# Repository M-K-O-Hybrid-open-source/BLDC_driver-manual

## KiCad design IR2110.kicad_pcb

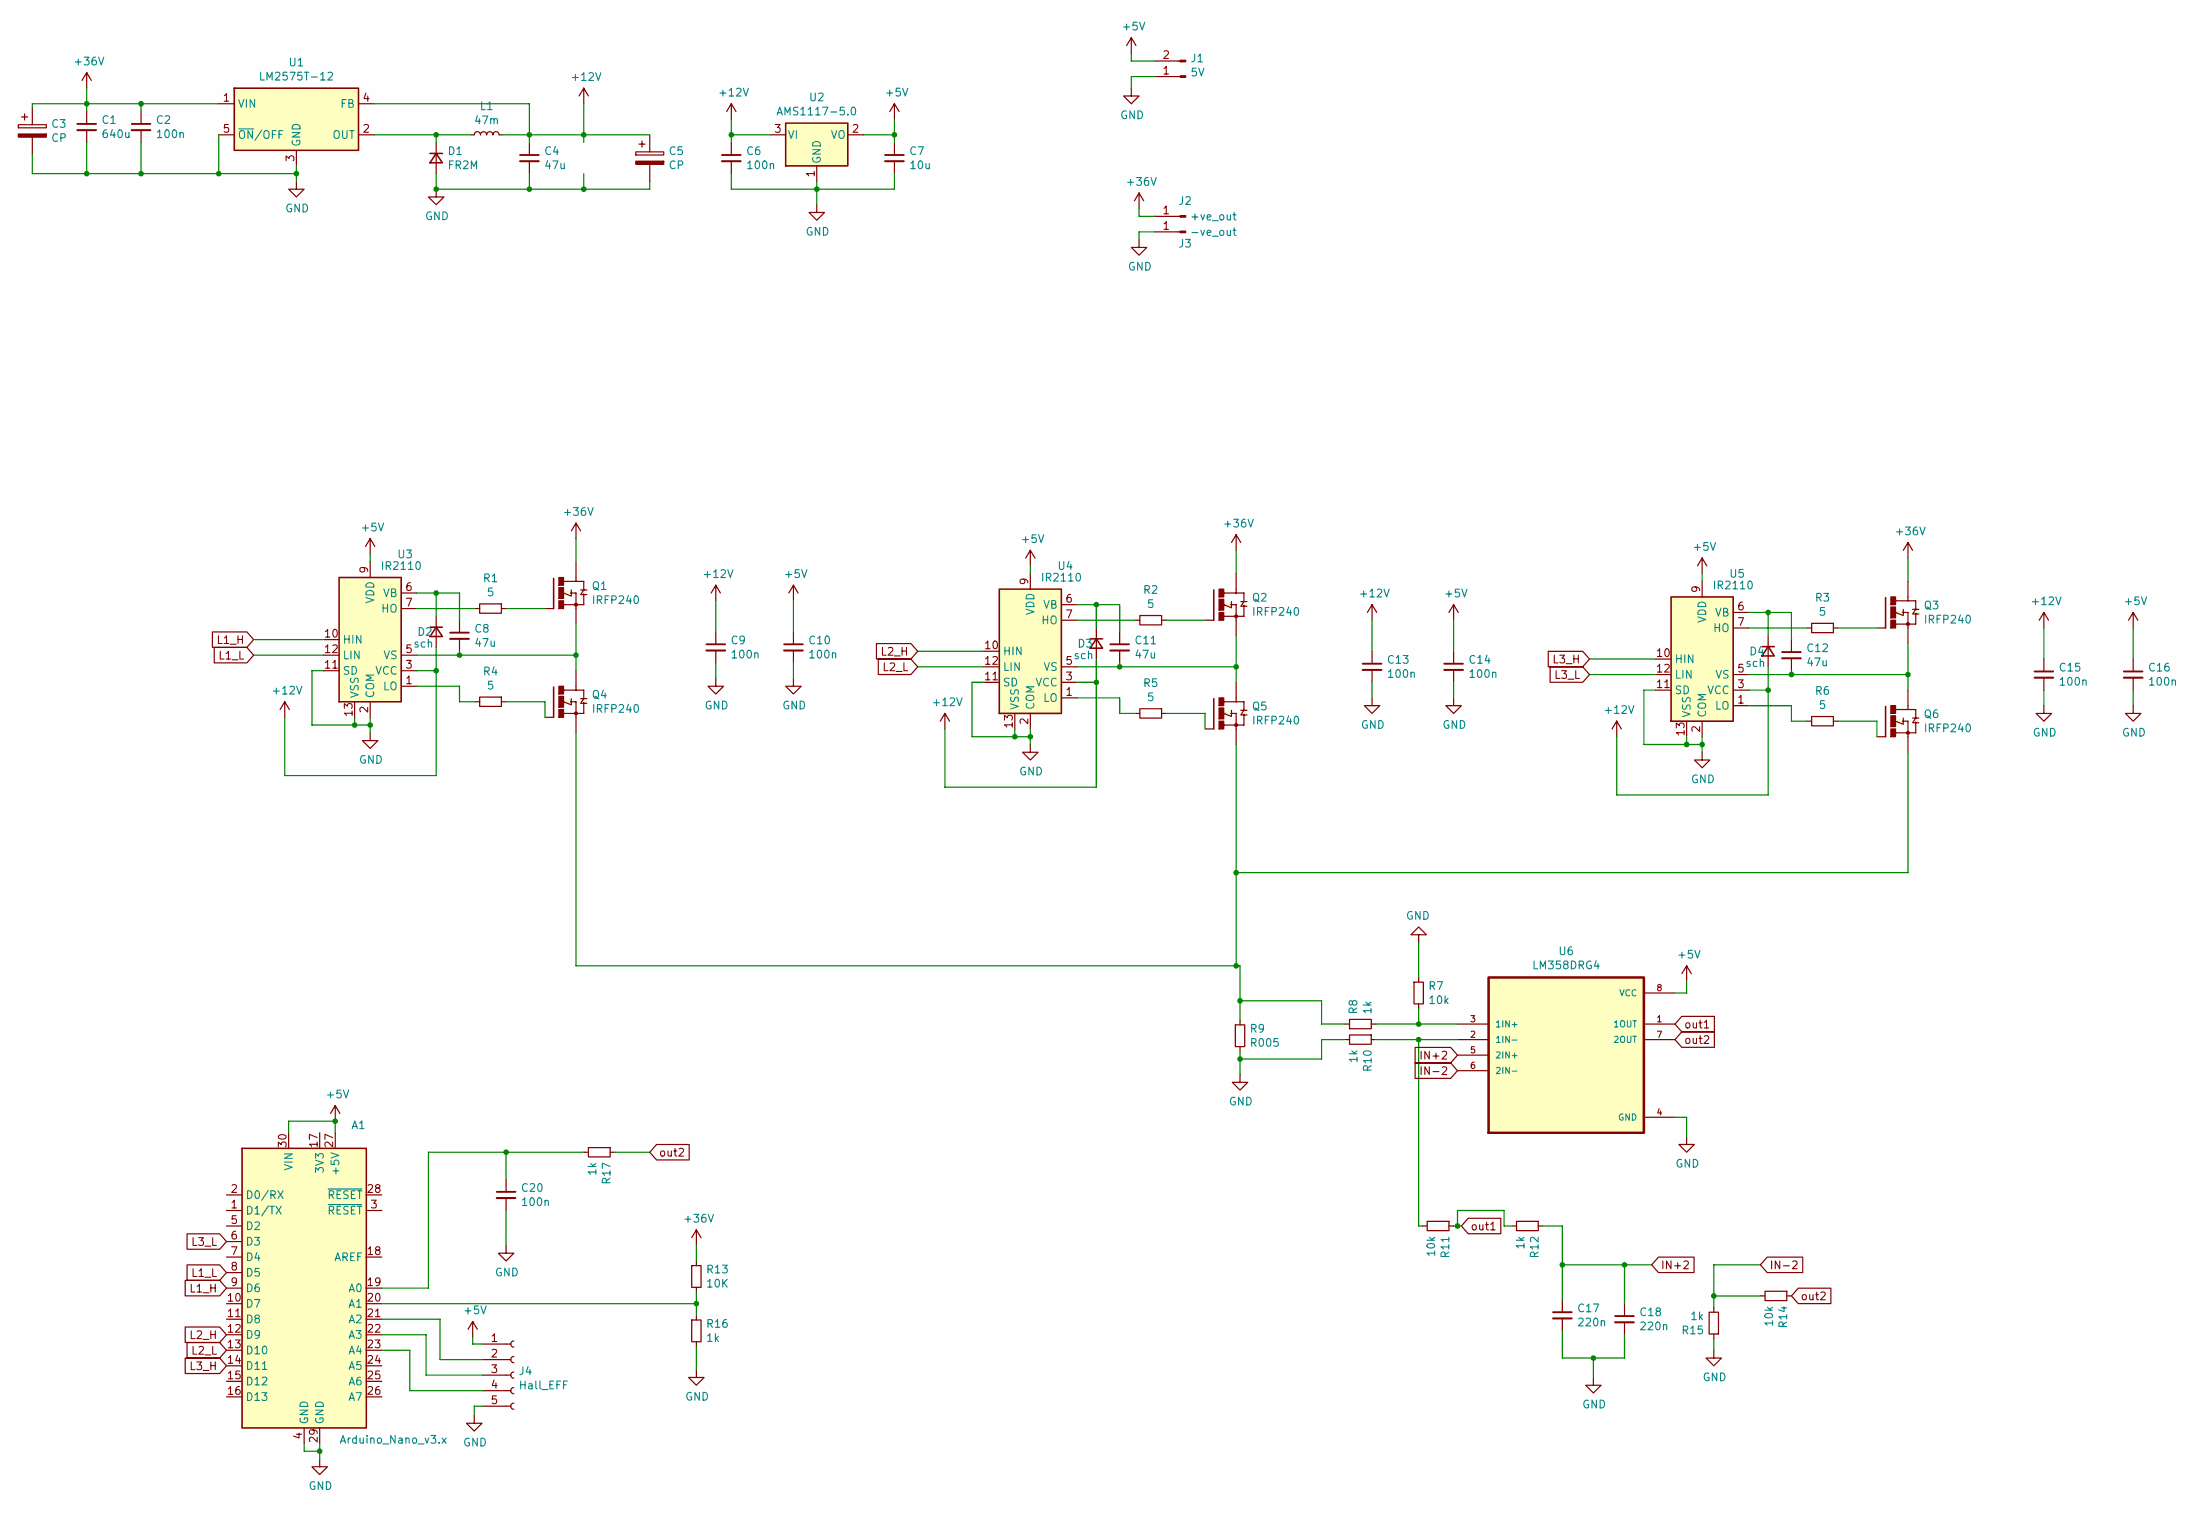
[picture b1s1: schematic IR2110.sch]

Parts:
A1: Arduino_Nano_v3.x; Arduino_Nano
C1: 640u; C_0805_2012Metric
C2, C6, C9, C10, C13, C14, C15, C16, C20: 100n; C_0805_2012Metric
C3, C5: CP; CP_Radial_D8.0mm_P5.00mm
C4, C8, C11, C12: 47u; C_0805_2012Metric
C7: 10u; C_0805_2012Metric
C17, C18: 220n; C_0805_2012Metric
D1: FR2M; D_SMB
D2, D3, D4: sch; D_SMB
J1: 5V; PinSocket_1x02_P2.54mm_Vertical
J2: +ve_out; SolderWirePad_1x01_SMD_1x2mm
J3: -ve_out; SolderWirePad_1x01_SMD_1x2mm
J4: Hall_EFF; PinHeader_1x05_P2.54mm_Vertical
L1: 47m; L_Toroid_Horizontal_D3.2mm_P6.40mm_Diameter3-5mm_Amidon-T12
Q1, Q2, Q3, Q4, Q5, Q6: IRFP240; TO-247-3_Vertical; PARTREV B
R1, R2, R3, R4, R5, R6: 5; R_Axial_DIN0204_L3.6mm_D1.6mm_P1.90mm_Vertical
R7, R11, R14: 10k; R_0805_2012Metric
R8, R10, R12, R15, R16, R17: 1k; R_0805_2012Metric
R9: R005; R_2512_6332Metric
R13: 10K; R_0805_2012Metric
U1: LM2575T-12; TO-220F-5_P3.4x3.7mm_StaggerEven_Lead3.5mm_Vertical
U2: AMS1117-5.0; SOT-223-3_TabPin2
U3, U4, U5: IR2110; DIP-14_W7.62mm
U6: LM358DRG4; SOIC127P599X175-8N

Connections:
+5V: A1.27 (+5V), A1.30 (VIN), C7.1, C10.1, C14.1, C16.1, J1.2, J4.1, U2.2 (VO), U3.9 (VDD), U4.9 (VDD), U5.9 (VDD), U6.8 (VCC)
+12V: C4.1, C5.1, C6.1, C9.1, C13.1, C15.1, D2.2 (A), D3.2 (A), D4.2 (A), L1.2, U1.4 (FB), U2.3 (VI), U3.3 (VCC), U4.3 (VCC), U5.3 (VCC)
+36V: C1.1, C2.1, C3.1, J2.1, Q1.2, Q2.2, Q3.2, R13.1, U1.1 (VIN)
GND: A1.4 (GND), A1.29 (GND), C1.2, C2.2, C3.2, C4.2, C5.2, C6.2, C7.2, C9.2, C10.2, C13.2, C14.2, C15.2, C16.2, C17.2, C18.2, C20.2, D1.2 (A), J1.1, J3.1, J4.5, R7.1, R9.2, R10.2, R15.1, R16.2, U1.3 (GND), U1.5 (~ON~/OFF), U2.1 (GND), U3.2 (COM), U3.11 (SD), U3.13 (VSS), U4.2 (COM), U4.11 (SD), U4.13 (VSS), U5.2 (COM), U5.11 (SD), U5.13 (VSS), U6.4 (GND)
IN+2: C17.1, C18.1, R12.1, U6.5 (2IN+)
IN-2: R14.2, R15.2, U6.6 (2IN-)
L1_H: A1.9 (D6), U3.10 (HIN)
L1_L: A1.8 (D5), U3.12 (LIN)
L2_H: A1.12 (D9), U4.10 (HIN)
L2_L: A1.13 (D10), U4.12 (LIN)
L3_H: A1.14 (D11), U5.10 (HIN)
L3_L: A1.6 (D3), U5.12 (LIN)
unnamed: A1.19 (A0), C20.1, R17.2
unnamed: A1.20 (A1), R13.2, R16.1
unnamed: A1.21 (A2), J4.2
unnamed: A1.22 (A3), J4.3
unnamed: A1.23 (A4), J4.4
unnamed: C8.1, D2.1 (K), U3.6 (VB)
unnamed: C8.2, Q1.3, Q4.2, U3.5 (VS)
unnamed: C11.1, D3.1 (K), U4.6 (VB)
unnamed: C11.2, Q2.3, Q5.2, U4.5 (VS)
unnamed: C12.1, D4.1 (K), U5.6 (VB)
unnamed: C12.2, Q3.3, Q6.2, U5.5 (VS)
unnamed: D1.1 (K), L1.1, U1.2 (OUT)
unnamed: Q1.1, R1.1
unnamed: Q2.1, R2.1
unnamed: Q3.1, R3.1
unnamed: Q4.1, R4.1
unnamed: Q4.3, Q5.3, Q6.3, R8.1, R9.1
unnamed: Q5.1, R5.1
unnamed: Q6.1, R6.1
unnamed: R1.2, U3.7 (HO)
unnamed: R2.2, U4.7 (HO)
unnamed: R3.2, U5.7 (HO)
unnamed: R4.2, U3.1 (LO)
unnamed: R5.2, U4.1 (LO)
unnamed: R6.2, U5.1 (LO)
unnamed: R7.2, R8.2, U6.3 (1IN+)
unnamed: R10.1, R11.2, U6.2 (1IN-)
out1: R11.1, R12.2, U6.1 (1OUT)
out2: R14.1, R17.1, U6.7 (2OUT)

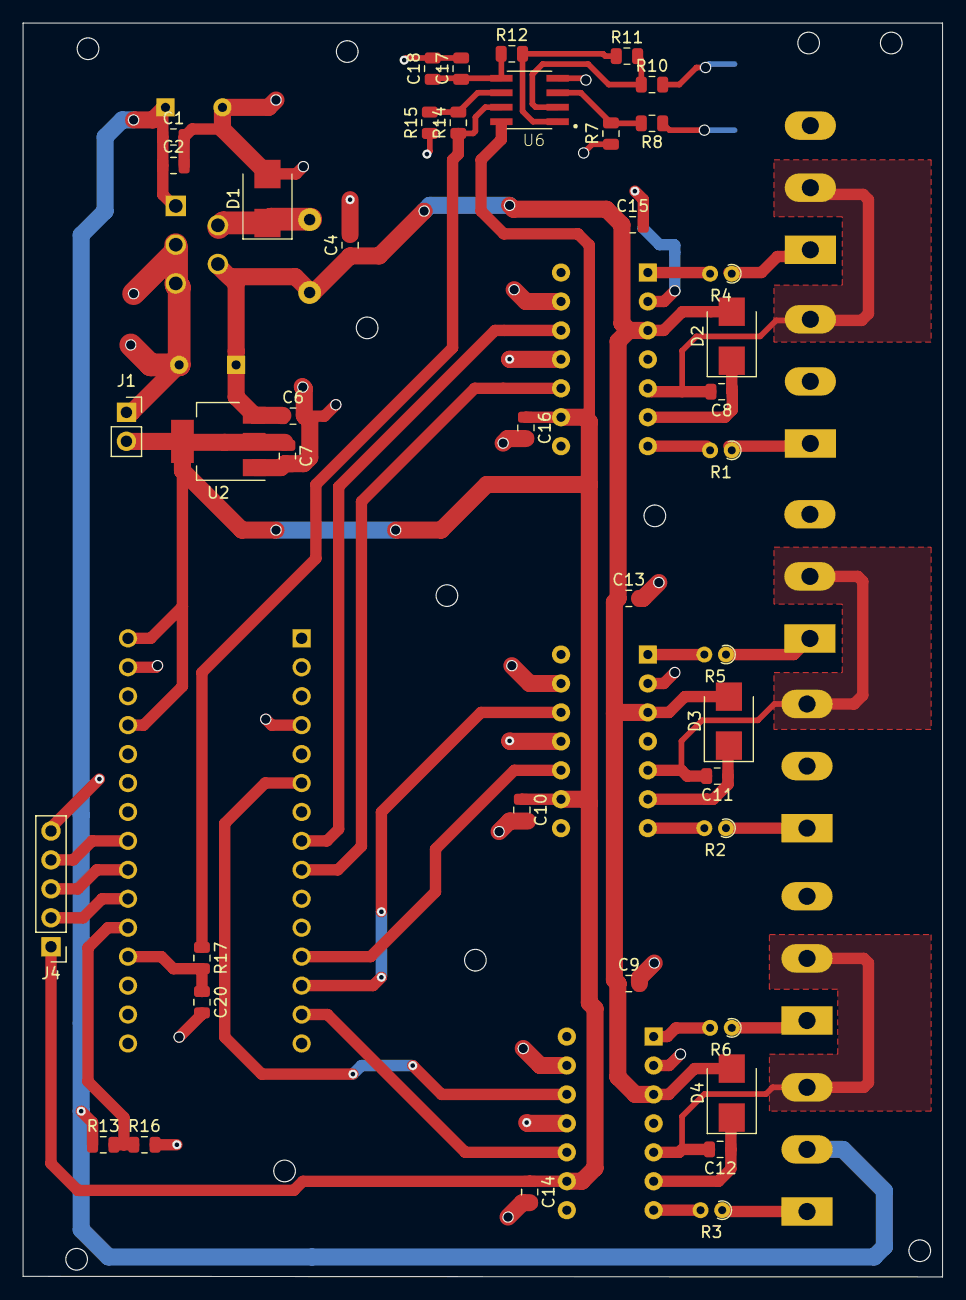
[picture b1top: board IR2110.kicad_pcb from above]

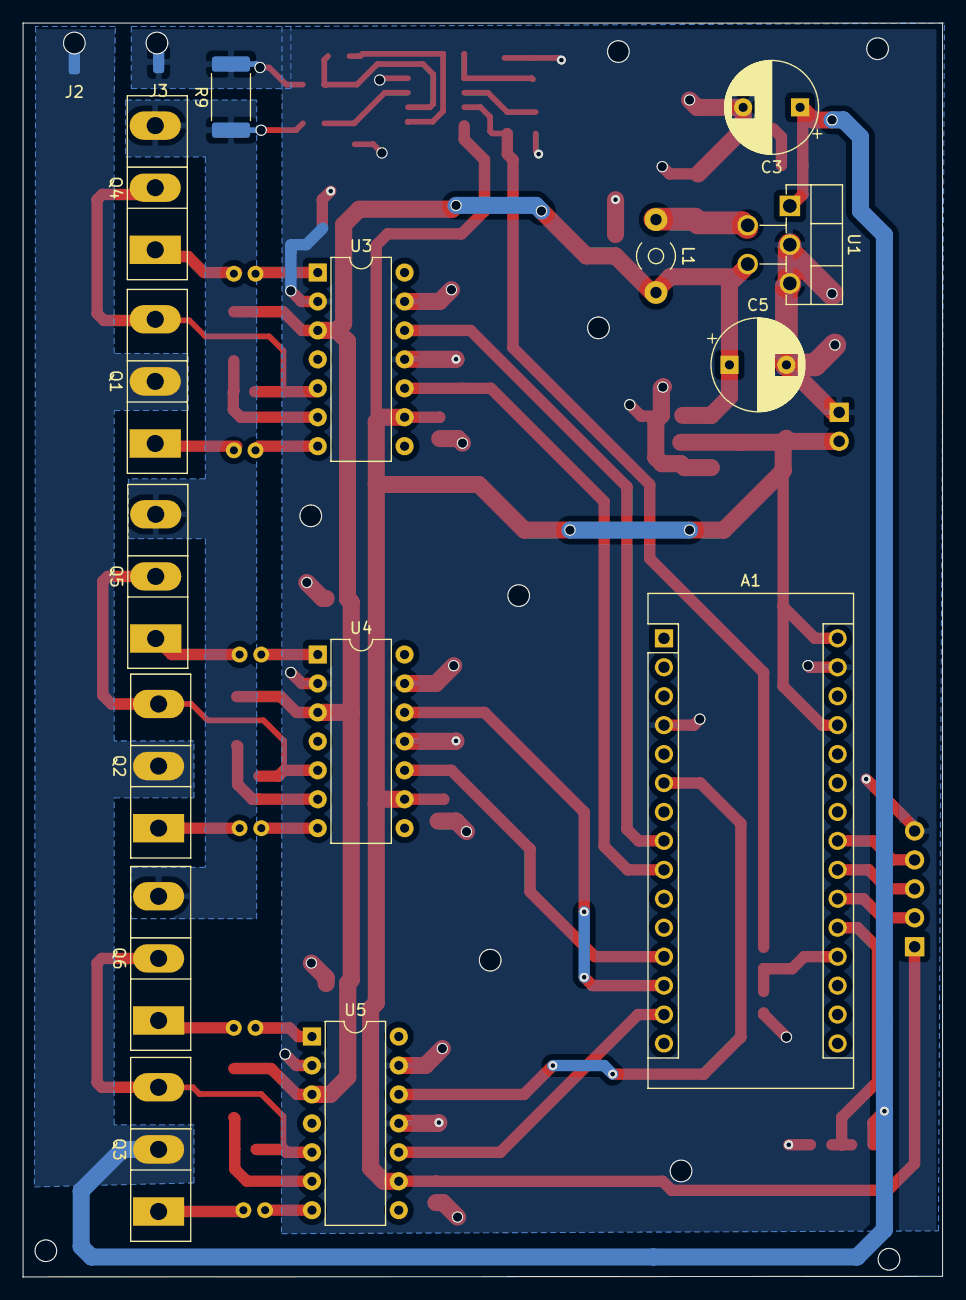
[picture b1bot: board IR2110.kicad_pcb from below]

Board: 2 copper layers, 80.7 x 110.1 mm, 58 parts (17 on the bottom side), 41 nets.
